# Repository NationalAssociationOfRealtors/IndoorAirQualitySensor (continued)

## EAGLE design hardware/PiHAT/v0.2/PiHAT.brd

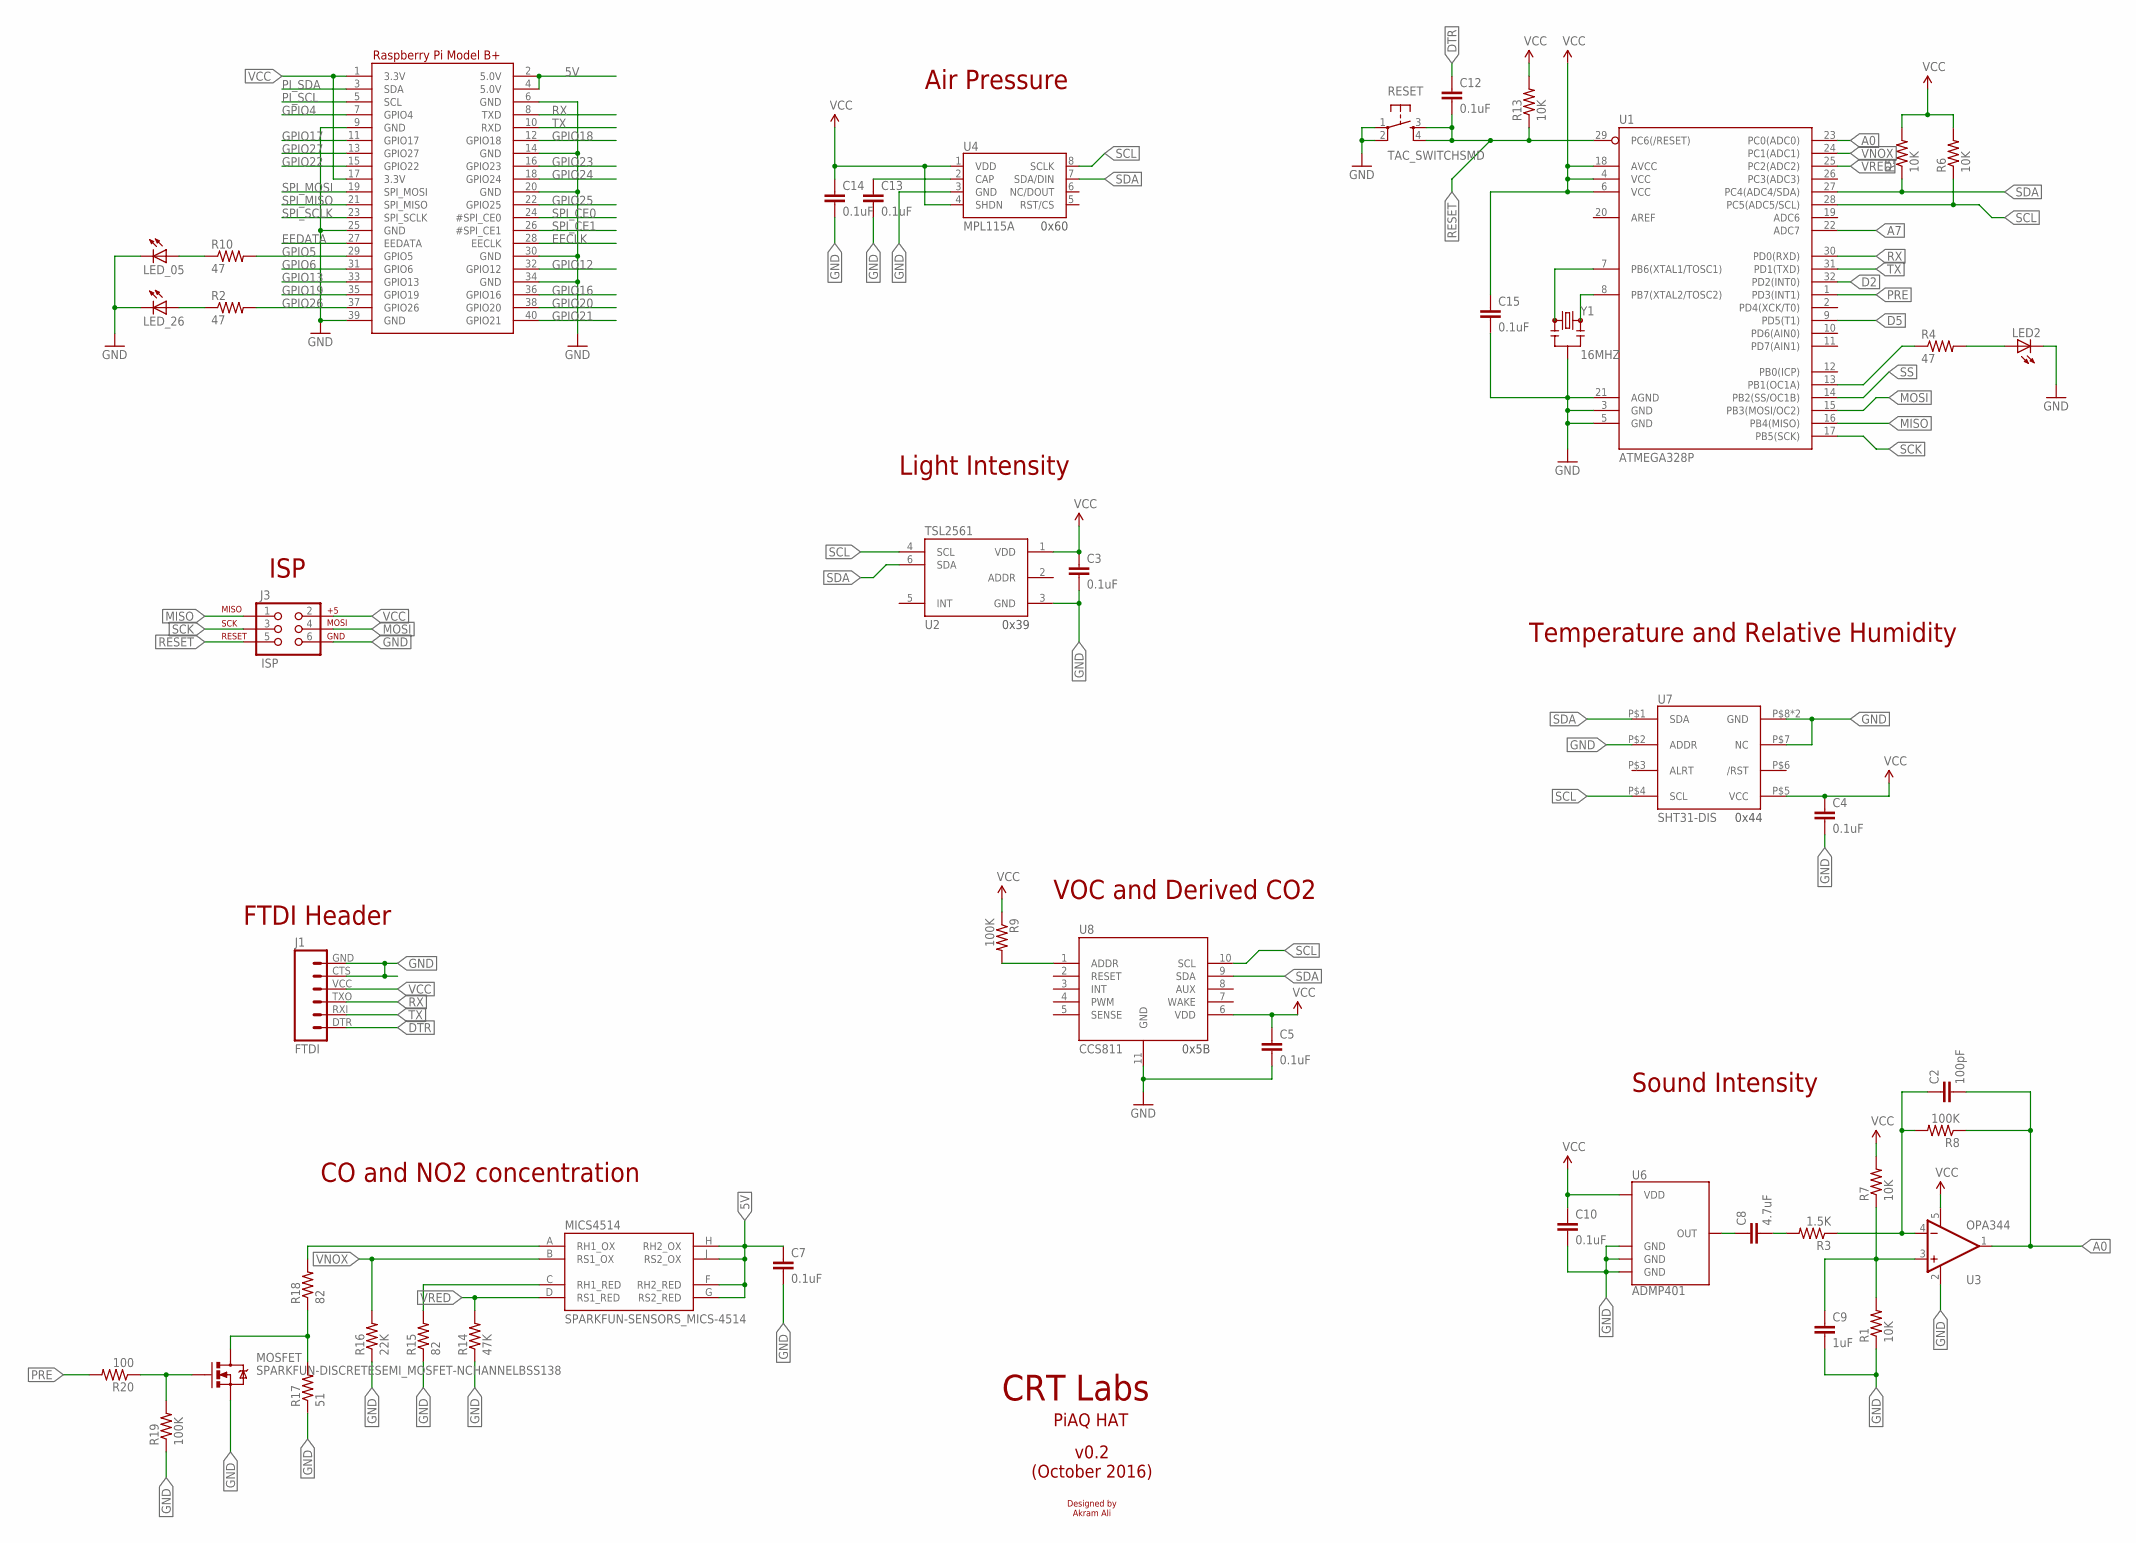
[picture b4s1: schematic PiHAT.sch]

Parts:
C2: 100pF; 0805; MPN CC0805JRNPO9BN101; DIGIKEY# 311-1111-1-ND
C3, C4, C5, C7, C10, C12, C13, C14, C15: 0.1uF; 0805; MPN CC0603KRX7R7BB104; DIGIKEY# 311-1088-1-ND
C8: 4.7uF; 0805; MPN CC0805KKX5R8BB475; DIGIKEY# 311-1871-1-ND
C9: 1uF; 0805; MPN CC0805KKX7R7BB105; DIGIKEY# 311-1365-1-ND
J1: FTDI; FTDI_BASIC; MPN FT231XS-R; DIGIKEY# 768-1129-1-ND
J3: ISP; 2X3
LED2: LEDCHIPLED_0805; CHIPLED_0805; MPN LY L29K-H1K2-26-Z; DIGIKEY# 475-1196-1-ND
LED_05, LED_26: LEDCHIPLED_0805; CHIPLED_0805; MPN LY L29K-H1K2-26-Z; DIGIKEY# 475-1196-1-ND
MICS4514: SPARKFUN-SENSORS_MICS-4514; SPARKFUN-SENSORS_MICS_10-SMD; MPN MiCS-4514
MOSFET: SPARKFUN-DISCRETESEMI_MOSFET-NCHANNELBSS138; SPARKFUN-DISCRETESEMI_SOT23-3; MPN BSS138-7-F; DIGIKEY# BSS138-FDICT-ND
R1, R5, R6, R7, R13: 10K; 0805; MPN RC0805JR-0710KL; DIGIKEY# 311-10KARCT-ND
R2, R4, R10: 47; 0805; MPN RC0805JR-0747RL; DIGIKEY# 311-47ARCT-ND
R3: 1.5K; 0805; MPN RT0805BRD071K5L; DIGIKEY# YAG1814CT-ND
R8, R9: 100K; 0805; MPN RC0805FR-07100KL; DIGIKEY# 541-82.0CCT-ND
R14: 47K; 0805; MPN ESR10EZPJ473; DIGIKEY# RHM47KKCT-ND
R15, R18: 82; 0805; MPN CRCW080582R0FKEA; DIGIKEY# 541-82.0CCT-ND
R16: 22K; 0805; MPN RC0805JR-0722KL; DIGIKEY# 311-22KARCT-ND
R17: 51; 0805; MPN ESR10EZPJ510; DIGIKEY# RHM51KCT-ND
R19: 100K; 0805; MPN RC0805FR-07100KL; DIGIKEY# 311-100KCRCT-ND
R20: 100; 0805; MPN RC0805FR-07100RL; DIGIKEY# 311-100CRCT-ND
RESET: TAC_SWITCHSMD; TACTILE-SWITCH-SMD; MPN PTS525SM15SMTR2 LFS; DIGIKEY# CKN9104CT-ND
RPI1: RASPBERRYPI_BPLUS_HATSLOTS; PI_HAT_SLOTS
U1: ATMEGA328P; TQFP32-08; MPN ATMEGA328PB-AU; DIGIKEY# ATMEGA328P-AU-ND
U2: TSL2561; FN-6; MOUSER# 856-TSL2561T; DIGIKEY# TSL2561-FNCT-ND
U3: OPA344; SOT23-5; MPN OPA344NA/3K; DIGIKEY# 296-41475-1-ND
U4: MPL115A; LGA8; MPN MPL115A2; DIGIKEY# MPL115A2-ND
U6: ADMP401; MPN INMP401ACEZ-R7; DIGIKEY# INMP401ACEZ-R7CT-ND
U7: SHT31-DIS; SHT3X; MPN SHT31-DIS-B; DIGIKEY# 1649-1011-1-ND
U8: CCS811; LGA; MPN CCS811
Y1: 16MHZ; RESONATOR-SMD; MPN CSTCE16M0V53-R0; DIGIKEY# 490-1198-1-ND

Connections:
5V: C7.1, MICS4514.F (RH2_RED), MICS4514.G (RS2_RED), MICS4514.H (RH2_OX), MICS4514.J (RS2_OX), RPI1.2 (5.0V), RPI1.4 (5.0V)
A0: C2.2, R8.1, U1.23 (PC0(ADC0)), U3.1 (OUT)
A7: U1.22 (ADC7)
D2: U1.32 (PD2(INT0))
D5: U1.9 (PD5(T1))
DTR: C12.1, J1.DTR (1)
EECLK: RPI1.28 (EECLK)
EEDATA: RPI1.27 (EEDATA)
GND: C3.2, C4.2, C5.2, C7.2, C9.2, C10.2, C13.2, C14.2, C15.2, J1.CTS (5), J1.GND (6), J3.6, LED2.C, LED_05.C, LED_26.C, MOSFET.2 (S), R1.1, R14.1, R15.1, R16.1, R17.1, R19.1, RESET.1, RESET.2, RPI1.6 (GND), RPI1.9 (GND), RPI1.14 (GND), RPI1.20 (GND), RPI1.25 (GND), RPI1.30 (GND), RPI1.34 (GND), RPI1.39 (GND), U1.3 (GND), U1.5 (GND), U1.21 (AGND), U2.3 (GND), U3.2 (V-), U4.3 (GND), U6.2 (GND), U6.4 (GND), U6.6 (GND), U7.P$2 (ADDR), U7.P$7 (NC), U7.P$8 (GND), U7.PAD (GND), U8.11 (GND), Y1.2
GPIO4: RPI1.7 (GPIO4)
GPIO5: R10.2, RPI1.29 (GPIO5)
GPIO6: RPI1.31 (GPIO6)
GPIO12: RPI1.32 (GPIO12)
GPIO13: RPI1.33 (GPIO13)
GPIO16: RPI1.36 (GPIO16)
GPIO17: RPI1.11 (GPIO17)
GPIO18: RPI1.12 (GPIO18)
GPIO19: RPI1.35 (GPIO19)
GPIO20: RPI1.38 (GPIO20)
GPIO21: RPI1.40 (GPIO21)
GPIO22: RPI1.15 (GPIO22)
GPIO23: RPI1.16 (GPIO23)
GPIO24: RPI1.18 (GPIO24)
GPIO25: RPI1.22 (GPIO25)
GPIO26: R2.2, RPI1.37 (GPIO26)
GPIO27: RPI1.13 (GPIO27)
MISO: J3.1, U1.16 (PB4(MISO))
MOSI: J3.4, U1.15 (PB3(MOSI/OC2))
unnamed: LED_26.A, R2.1
unnamed: R4.1, U1.13 (PB1(OC1A))
unnamed: LED2.A, R4.2
unnamed: U1.8 (PB7(XTAL2/TOSC2)), Y1.3
unnamed: U1.7 (PB6(XTAL1/TOSC1)), Y1.1
unnamed: LED_05.A, R10.1
unnamed: C8.1, U6.1 (OUT)
unnamed: MICS4514.A (RH1_OX), R18.2
unnamed: C8.2, R3.2
unnamed: C2.1, R3.1, R8.2, U3.4 (-IN)
unnamed: C9.1, R1.2, R7.1, U3.3 (+IN)
unnamed: C13.1, U4.2 (CAP)
unnamed: MICS4514.C (RH1_RED), R15.2
unnamed: R9.2, U8.1 (ADDR)
unnamed: MOSFET.3 (D), R17.2, R18.1
unnamed: MOSFET.1 (G), R19.2, R20.1
PI_SCL: RPI1.5 (SCL)
PI_SDA: RPI1.3 (SDA)
PRE: R20.2, U1.1 (PD3(INT1))
RESET: C12.2, J3.5, R13.1, RESET.3, RESET.4, U1.29 (PC6(/RESET))
RX: J1.TXO (3), RPI1.8 (TXD), U1.30 (PD0(RXD))
SCK: J3.3, U1.17 (PB5(SCK))
SCL: R6.1, U1.28 (PC5(ADC5/SCL)), U2.4 (SCL), U4.8 (SCLK), U7.P$4 (SCL), U8.10 (SCL)
SDA: R5.1, U1.27 (PC4(ADC4/SDA)), U2.6 (SDA), U4.7 (SDA/DIN), U7.P$1 (SDA), U8.9 (SDA)
SPI_CE0: RPI1.24 (#SPI_CE0)
SPI_CE1: RPI1.26 (#SPI_CE1)
SPI_MISO: RPI1.21 (SPI_MISO)
SPI_MOSI: RPI1.19 (SPI_MOSI)
SPI_SCLK: RPI1.23 (SPI_SCLK)
SS: U1.14 (PB2(SS/OC1B))
TX: J1.RXI (2), RPI1.10 (RXD), U1.31 (PD1(TXD))
VCC: C3.1, C4.1, C5.1, C10.1, C14.1, C15.1, J1.VCC (4), J3.2, R5.2, R6.2, R7.2, R9.1, R13.2, RPI1.1 (3.3V), RPI1.17 (3.3V), U1.4 (VCC), U1.6 (VCC), U1.18 (AVCC), U2.1 (VDD), U3.5 (V+), U4.1 (VDD), U4.4 (SHDN), U6.5 (VDD), U7.P$5 (VCC), U8.6 (VDD)
VNOX: MICS4514.B (RS1_OX), R16.2, U1.24 (PC1(ADC1))
VRED: MICS4514.D (RS1_RED), R14.2, U1.25 (PC2(ADC2))

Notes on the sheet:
Light Intensity
VOC and Derived CO2
Air Pressure
Sound Intensity
Temperature and Relative Humidity
ISP
CO and NO2 concentration
CRT Labs
PiAQ HAT
v0.2 (October 2016)
Designed by Akram Ali
0x39
0x60
0x5B
0x44
FTDI Header

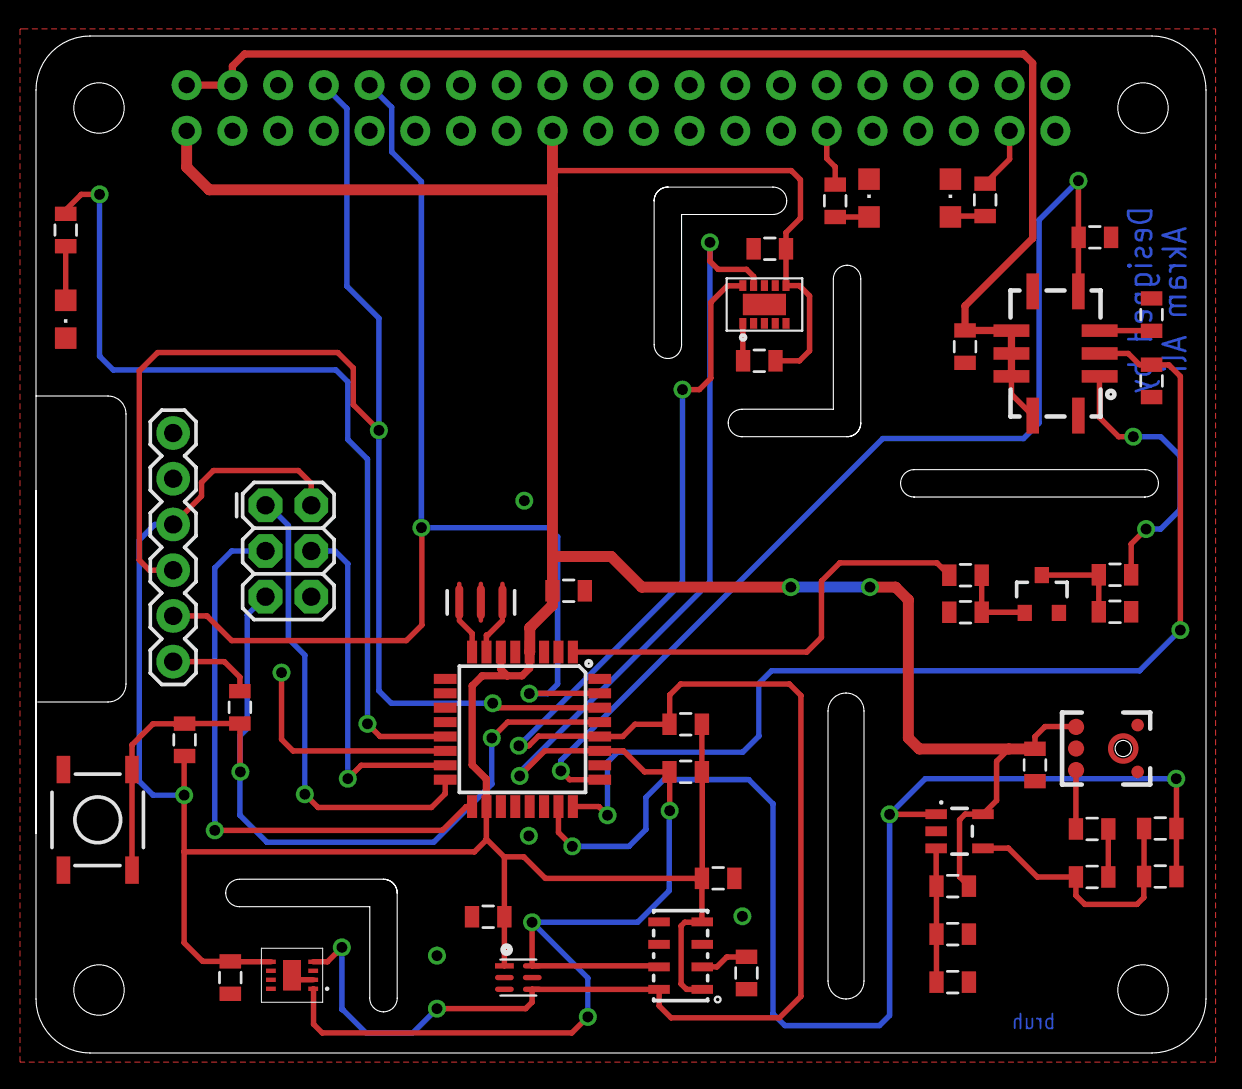
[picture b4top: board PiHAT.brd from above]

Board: 2 copper layers, 65.0 x 56.5 mm, 47 parts (0 on the bottom side), 34 nets.

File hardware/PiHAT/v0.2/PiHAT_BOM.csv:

Part,Value,Device,Package,Description,DIGIKEY#,MANF,MANF#,MF,MOUSER#,MPN,NO_BOM
C2,100pF,CAP0805,805,Capacitor,311-1111-1-ND,,,,,CC0805JRNPO9BN101,
C3,0.1uF,CAP0805,805,Capacitor,311-1088-1-ND,,,,,CC0603KRX7R7BB104,
C4,0.1uF,CAP0805,805,Capacitor,311-1088-1-ND,,,,,CC0603KRX7R7BB104,
C5,0.1uF,CAP0805,805,Capacitor,311-1088-1-ND,,,,,CC0603KRX7R7BB104,
C7,0.1uF,CAP0805,805,Capacitor,311-1088-1-ND,,,,,CC0603KRX7R7BB104,
C8,4.7uF,CAP0805,805,Capacitor,311-1871-1-ND,,,,,CC0805KKX5R8BB475,
C9,1uF,CAP0805,805,Capacitor,311-1365-1-ND,,,,,CC0805KKX7R7BB105,
C10,0.1uF,CAP0805,805,Capacitor,311-1088-1-ND,,,,,CC0603KRX7R7BB104,
C12,0.1uF,CAP0805,805,Capacitor,311-1088-1-ND,,,,,CC0603KRX7R7BB104,
C13,0.1uF,CAP0805,805,Capacitor,311-1088-1-ND,,,,,CC0603KRX7R7BB104,
C14,0.1uF,CAP0805,805,Capacitor,311-1088-1-ND,,,,,CC0603KRX7R7BB104,
C15,0.1uF,CAP0805,805,Capacitor,311-1088-1-ND,,,,,CC0603KRX7R7BB104,
J1,FTDI,FTDI_BASICPTH,FTDI_BASIC,FTDI Basic header with labels,768-1129-1-ND,,,,,FT231XS-R,
LED2,,LEDCHIPLED_0805,CHIPLED_0805,LED,475-1196-1-ND,,,,,LY L29K-H1K2-26-Z,
LED_05,,LEDCHIPLED_0805,CHIPLED_0805,LED,475-1196-1-ND,,,,,LY L29K-H1K2-26-Z,
LED_26,,LEDCHIPLED_0805,CHIPLED_0805,LED,475-1196-1-ND,,,,,LY L29K-H1K2-26-Z,
MICS4514,SPARKFUN-SENSORS_MICS-4514,SPARKFUN-SENSORS_MICS-4514,SPARKFUN-SENSORS_MICS_10-SMD,Metal oxide MEMS carbon monoxide (CO) and NOx sensor in an SMD package.,,SensorTech,,,,MiCS-4514,
MOSFET,SPARKFUN-DISCRETESEMI_MOSFET-NCHANNELBSS138,SPARKFUN-DISCRETESEMI_MOSFET-NCHANNELBSS138,SPARKFUN-DISCRETESEMI_SOT23-3,Common NMOSFET Parts,BSS138-FDICT-ND,,,,,BSS138-7-F,
R1,10K,RESISTOR0805-RES,805,Resistor,311-10KARCT-ND,,,,,RC0805JR-0710KL,
R2,47,RESISTOR0805-RES,805,Resistor,311-47ARCT-ND,,,,,RC0805JR-0747RL,
R3,1.5K,RESISTOR0805-RES,805,Resistor,YAG1814CT-ND,,,,,RT0805BRD071K5L,
R4,47,RESISTOR0805-RES,805,Resistor,311-47ARCT-ND,,,,,RC0805JR-0747RL,
R5,10K,RESISTOR0805-RES,805,Resistor,311-10KARCT-ND,,,,,RC0805JR-0710KL,
R6,10K,RESISTOR0805-RES,805,Resistor,311-10KARCT-ND,,,,,RC0805JR-0710KL,
R7,10K,RESISTOR0805-RES,805,Resistor,311-10KARCT-ND,,,,,RC0805JR-0710KL,
R8,100K,RESISTOR0805-RES,805,Resistor,541-82.0CCT-ND,,,,,RC0805FR-07100KL,
R9,100K,RESISTOR0805-RES,805,Resistor,541-82.0CCT-ND,,,,,RC0805FR-07100KL,
R10,47,RESISTOR0805-RES,805,Resistor,311-47ARCT-ND,,,,,RC0805JR-0747RL,
R13,10K,RESISTOR0805-RES,805,Resistor,311-10KARCT-ND,,,,,RC0805JR-0710KL,
R14,47K,RESISTOR0805-RES,805,Resistor,RHM47KKCT-ND,,,,,ESR10EZPJ473,
R15,82,RESISTOR0805-RES,805,Resistor,541-82.0CCT-ND,,,,,CRCW080582R0FKEA,
R16,22K,RESISTOR0805-RES,805,Resistor,311-22KARCT-ND,,,,,RC0805JR-0722KL,
R17,51,RESISTOR0805-RES,805,Resistor,RHM51KCT-ND,,,,,ESR10EZPJ510,
R18,82,RESISTOR0805-RES,805,Resistor,541-82.0CCT-ND,,,,,CRCW080582R0FKEA,
R19,100K,RESISTOR0805-RES,805,Resistor,311-100KCRCT-ND,,,,,RC0805FR-07100KL,
R20,100,RESISTOR0805-RES,805,Resistor,311-100CRCT-ND,,,,,RC0805FR-07100RL,
RESET,TAC_SWITCHSMD,TAC_SWITCHSMD,TACTILE-SWITCH-SMD,Momentary Switch,CKN9104CT-ND,,,,,PTS525SM15SMTR2 LFS,
U1,ATMEGA328P,ATMEGA328P_TQFP,TQFP32-08,,ATMEGA328P-AU-ND,,,,,ATMEGA328PB-AU,
U2,TSL2561,TSL2561FN,FN-6,TSL2561 illumination sensor,TSL2561-FNCT-ND,AMS-TAOS-USA-Inc.,TSL2561FN,,856-TSL2561T,TSL2561FN,
U3,OPA344,OPA344,SOT23-5,Single gate rail-to-rail output op-amp. Inputs extend 300mV past rails.,296-41475-1-ND,,,,,OPA344NA/3K,
U4,MPL115A,MPL115A,LGA8,MPL115A1 (SPI) and MPL115A2 (I2C) Miniature Digital Barometer,MPL115A2-ND,,,,,MPL115A2,
U6,ADMP401,ADMP401,ADMP401,Omnidirection bottom-port MEMS microphone,INMP401ACEZ-R7CT-ND,,,,,INMP401ACEZ-R7,
U7,SHT31-DIS,SHT31-DIS,SHT3X,,1649-1011-1-ND,,,,,SHT31-DIS-B,
U8,CCS811,CCS811-I2C,LGA,,,AMS,,,,CCS811,
Y1,16MHZ,RESONATOR16MHZ,RESONATOR-SMD,Resonator,490-1198-1-ND,,,,,CSTCE16M0V53-R0,

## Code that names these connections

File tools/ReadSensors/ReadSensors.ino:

/*
  Sensor Board v0.3
  Measures Temperature, Relative Humidity, Light intensity,
  Air pressure (and derived altitude), Sound intensity,
  concentrations of CO, NO2, VOC (derived) and CO2 (derived)

  Currently untested: TSL2561 light sensor code
  Currently untested: MAX4466 mic + amp code
  
  Designed at CRT Labs (July 2016)
  https://github.com/NationalAssociationOfRealtors/SensorBoard
  
  Modified: 6 September 2016
  by Akram Ali
 */

// define libraries
#include <Arduino.h>
#include <Wire.h>
#include "Adafruit_SHT31.h"
#include "SparkFunMPL3115A2.h"
#include <Adafruit_Sensor.h>
#include <Adafruit_TSL2561_U.h>

// define objects
MPL3115A2 myPressure;
Adafruit_SHT31 sht31 = Adafruit_SHT31();
Adafruit_TSL2561_Unified tsl = Adafruit_TSL2561_Unified(TSL2561_ADDR_FLOAT, 12345);

// define IAQ core global variables
#define iaqaddress 0x5A
uint16_t predict;
uint8_t statu;
int32_t resistance;
uint16_t tvoc;

// define MICS-4514 global variables
#define PRE_PIN          8
#define VNOX_PIN         A0
#define VRED_PIN         A1
#define PRE_HEAT_SECONDS 10
int vnox_value = 0;
int vred_value = 0;

// define TSL2561 global variables
long lux;

void setup()
{
  Serial.begin(115200);
  Serial.println("Setup");

  pinMode(9, OUTPUT);  // pin 9 controls LED
  pinMode(5, OUTPUT);   // pin 5 controls power to all sensors
  digitalWrite(5, HIGH);  // turn all sensors on
  delay(10);

  pinMode(PRE_PIN, OUTPUT);  // set preheater pin for mics4514 gas sensor
  Serial.print("MICS-4514 Preheating...");
  // Wait for preheating
  digitalWrite(PRE_PIN, 1);
  delay(PRE_HEAT_SECONDS * 1000);
  digitalWrite(PRE_PIN, 0);
  Serial.println("Done");
  
}

// the loop function runs over and over again forever
void loop()
{
  digitalWrite(9, HIGH);   // turn the LED on (HIGH is the voltage level)
  delay(1000);              // wait for a second
  digitalWrite(9, LOW);    // turn the LED off by making the voltage LOW
  
  Serial.println("---------------------");
  
  // MAX 4466 amp
  //Serial.println(analogRead(A0));  // read sound levels
  //Serial.println();


  // TSL2561 light sensor
  tsl.begin(); 
  tsl.enableAutoRange(true);
  //tsl.setIntegrationTime(TSL2561_INTEGRATIONTIME_13MS);      /* fast but low resolution */
  tsl.setIntegrationTime(TSL2561_INTEGRATIONTIME_101MS);  /* medium resolution and speed   */
  // tsl.setIntegrationTime(TSL2561_INTEGRATIONTIME_402MS);  /* 16-bit data but slowest conversions */
  sensors_event_t event;
  tsl.getEvent(&event);
  if (event.light)
    lux = event.light;
  else
    lux = -1;
  Serial.print("Light intensity (lux): ");
  Serial.println(lux);
  
  // MICS 4514 CO/NO2 gas sensor
  // Read analog values, print them out, and wait
  vnox_value = analogRead(VNOX_PIN);
  vred_value = analogRead(VRED_PIN);
  Serial.print("Vnox: ");
  Serial.print(vnox_value, DEC);
  Serial.print(" Vred: ");
  Serial.println(vred_value, DEC);
  readCO();
  readNO2();

  
  // MPL3115A2 air pressure sensor
  myPressure.begin(); // Get pressure sensor online
  //Configure the sensor
  //myPressure.setModeAltimeter(); // Measure altitude above sea level in meters
  myPressure.setModeBarometer(); // Measure pressure in Pascals from 20 to 110 kPa
  
  myPressure.setOversampleRate(7); // Set Oversample to the recommended 128
  myPressure.enableEventFlags(); // Enable all three pressure and temp event flags 
  delay(10);
  
  float pressure = myPressure.readPressure();
  Serial.print("MPL3115A2 Pressure(Pa): ");
  Serial.println(pressure, 2);

  float temperature = myPressure.readTempF();
  Serial.print("MPL3115A2 Temp(f): ");
  Serial.println(temperature, 2);

  //const int station_elevation_ft = 5374; //Must be obtained with a GPS unit
  //float station_elevation_m = station_elevation_ft * 0.3048; //I'm going to hard code this
  const int station_elevation_m = 1638; //Accurate for the roof on my house
  //1 pascal = 0.01 millibars
  pressure /= 100; //pressure is now in millibars

  float part1 = pressure - 0.3; //Part 1 of formula
  
  const float part2 = 8.42288 / 100000.0;
  float part3 = pow((pressure - 0.3), 0.190284);
  float part4 = (float)station_elevation_m / part3;
  float part5 = (1.0 + (part2 * part4));
  float part6 = pow(part5, (1.0/0.190284));
  float altimeter_setting_pressure_mb = part1 * part6; //Output is now in adjusted millibars
  float baroin = altimeter_setting_pressure_mb * 0.02953;

  Serial.print("MPL3115A2 Altimeter setting InHg: ");
  Serial.println(baroin, 2);

  
  // SHT31 T/RH sensor 
  sht31.begin(0x44);
  Serial.print("SHT31 Temperature: ");
  Serial.println(sht31.readTemperature());
  Serial.print("SHT31 Humidity: ");
  Serial.println(sht31.readHumidity());
  

  // IAQ core
  Wire.requestFrom(iaqaddress, 9);
  predict = (Wire.read()<< 8 | Wire.read()); 
  statu = Wire.read();
  resistance = (Wire.read()& 0x00)| (Wire.read()<<16)| (Wire.read()<<8| Wire.read());
  tvoc = (Wire.read()<<8 | Wire.read());
  checkStatus();
  
  Serial.print("CO2 concentration:");
  Serial.println(predict);
  //Serial.print("IAQ core Status: ");
  //Serial.println(statu, HEX);
  Serial.print("IAQ core Resistance: ");
  Serial.println(resistance);
  Serial.print("TVoC concentration: ");
  Serial.println(tvoc);

  
  Serial.println();
  
  //digitalWrite(5, LOW);  // turn sensors off
  delay(5000);
}



void checkStatus()
{
  if(statu == 0x10)
  {
    Serial.println("IAQ Core Warming up...");
  }
  else if(statu == 0x00)
  {
    Serial.println("IAQ Core Ready");  
  }
  else if(statu == 0x01)
  {
    Serial.println("IAQ Core Busy");  
  }
  else if(statu == 0x80)
  {
    Serial.println("IAQ Core Error");  
  }
  else
  Serial.println("No Status, check IAQ Core");  
}



float readCO()
{
  float adc = analogRead(VNOX_PIN);
  float Rs = 47000.0/(1023.0/adc);
  float R0 = 82000.0;
  float ratio = Rs/R0;
  float concentration = ((-181.4)*log(ratio))-97.469;
  Serial.print("CO concentration (ppb): ");
  //Serial.println(adc);
  //Serial.println(Rs);
  //Serial.println(R0);
  //Serial.println(ratio);
  Serial.println(concentration);
  return concentration;
}

float readNO2()
{
  float adc = analogRead(VRED_PIN);
  float Rs = 22000.0/(1023.0/adc);
  float R0 = 350.0;
  float ratio = Rs/R0;
  float concentration = (124.28*log(ratio))-270.37;
  Serial.print("NO2 concentration (ppb): ");
  //Serial.println(adc);
  //Serial.println(Rs);
  //Serial.println(R0);
  //Serial.println(ratio);
  Serial.println(concentration);
  return concentration;
}

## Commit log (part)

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2016-07-27 Eagle files for sensor board
2016-07-28 Replaced 5V stepup with reg
    Replaced NCP1402 with MCP1703 (for MICS 4514 gas sensor)
2016-08-10 Adding Case Design and STL
2016-08-11 adding honeycomb airflow
2016-08-11 code cleanup
2016-08-11 added rounded corners, dir struxture
2016-08-11 flipping for easier print
2016-08-11 added slot for pinouts
2016-08-11 adding eagle lock files to ignore
2016-08-11 adding new stl
2016-08-12 logo text on side of case
2016-08-16 adding slide cover
2016-08-25 added labels to board and ftdi mapping instructions
2016-08-25 formatting
2016-09-06 Sensor board v0.2 Arduino test code
    Read all data in serial monitor.
    Untested: TSL2561
    Untested: MAX4466
2016-09-06 Replaced mic
2016-09-07 Added RFM69 pads, FTDI chip, USB-microB, bug fixes
2016-09-07 first commit of radio board
2016-09-07 Changed font size of labels
2016-09-08 updating git ignore with eagle lock files
2016-09-08 directory organization
2016-09-08 adding professional shots and updating readme
2016-09-08 updating description
2016-09-08 adding capabilities to README
2016-09-08 adding tool to read sensor data for initial testing
2016-09-08 prepping for hardware version 3.0
2016-09-08 adding license
2016-09-08 adding v3 images
2016-09-08 Updating license to Apache 2
2016-09-08 modifying v3 enclosure and fixing typo on sensor board v3 schematic
2016-09-08 OSH Park render
2016-09-08 Moved hidden labels to tNames layer
2016-09-08 Moved labels to _tsilk layer (121)
2016-09-08 Added PDF schematic
2016-09-08 Adjusted some traces
2016-09-09 Added SMA connector for antenna
2016-09-09 Minor touches
2016-09-09 Removed 'label' from SMA connector
2016-09-09 Added v0.4 OSH park render
2016-09-09 Update README.md
    Added sensor model numbers
2016-09-10 syntax on scad
2016-09-10 naming conventions
2016-09-10 fixed link
2016-09-14 Created v0.5
2016-09-14 Removed NPN transistor
    connected everything to common GND
2016-09-14 Increased thickness of power lines to 16
2016-09-14 Added decoupling cap for ATmega328P
    0.1uF
2016-09-14 Rearranged status LED
    and decoupling cap
2016-09-14 Added extra GND vias
2016-09-14 Adjusted some traces around MCU
2016-09-14 Added v0.5 PDF schematic
2016-09-15 Made the GND plane more consistent
2016-09-15 Connected GND plane
2016-09-15 Added PiHAT
2016-09-15 Removed FTDI, RFM69, USB
2016-09-15 started mapping sensors for pi hat
2016-09-16 Minor touch up of some traces
    near TSL2561 and SHT31
2016-09-16 Verrrrrry minor adjustments
    ¯\_(ツ)_/¯
2016-09-19 sensor board BOM
2016-09-19 Fixed several traces
2016-09-19 Updated silkscreen
2016-09-19 Added CRT Labs logo, gerber files
2016-09-23 Rename
2016-09-26 Added v0.3 photo
2016-09-27 Added sensor board node firmware
2016-09-28 Moved Trace on PiAQ, v4 of enclosure
2016-09-29 updating bom and iaq-case v4
2016-10-03 v0.6 - Major design update
    - Added CCS811 gas sensor (replaced IAQ core)
    - Added thermal isolation for all sensors
    - Rearranged all components to accommodate for thermal isolation
    - Ripped up all traces and rerouted them based on new arrangement
    - Temporarily removed ADMP401 mic + opamp (previous design was
    incorrect; requires envelop follower circuit for sound intensity
2016-10-05 Create master branch via GitHub
2016-10-05 Update CNAME
2016-10-05 organizing web directory
2016-10-05 v0.1 of piaq.io
2016-10-05 started adding links to schematics and data sheets
2016-10-05 adding images
2016-10-05 added link to board
2016-10-05 continuing to add BOM materials
2016-10-05 removing chars from BOM
2016-10-05 updating descriptions on bom
2016-10-05 adding piaq to home page
2016-10-05 updating faq
2016-10-05 finishing up faq
2016-10-05 typo fix
2016-10-05 Added 5x2 header attribute
    Digikey part number
2016-10-05 Updated BOM
    Digikey part number for MOSFET
2016-10-05 adding Photo Booth pics
2016-10-05 rolling in new photos
2016-10-05 spacing
2016-10-06 updated photo
    color corrected
2016-10-06 updated photos
    color corrected/full rez
2016-10-06 reorganizing photos
2016-10-06 rename file
2016-10-06 change images
    new color corrected images
2016-10-06 Moved files to separate folder
    v0.1
2016-10-06 adding head to faq page
2016-10-06 Updated PiAQ HAT to v0.2
    - Added LEDs on GPIO 05, 26
    - Replaced IAQ Core with CCS811
    - Added more thermal isolation and rerouted traces
    - Minor silkscreen adjustments
2016-10-06 Minor fixes to sensor board v0.6
2016-10-06 Added environmental parameters to silkscreen
2016-10-06 Minor trace fix
2016-10-06 Trace adjustments
2016-10-06 I2C pullups silkscreen
2016-10-06 Fixed layers
2016-10-06 Added FTDI headers to Pi HAT, separated ISP headers
2016-10-06 removed dupe data sheet
2016-10-06 Power trace adjustment
2016-10-06 v0.7 - Added mounting holes to the board
    - Dimension change
    - curved edges
2016-10-06 Adjusted microUSB port towards the edge
2016-10-06 cap trace adjustment
2016-10-07 v2 gerber files
2016-10-07 adding MPN to v2 schematics
2016-10-07 Sensor Node Photo
2016-10-07 adding details to aid in fabrication
2016-10-11 Renamed file names for each version
2016-10-18 v0.8 - Replaced MPL3115A2 with BMP280
    BMP280 is lower power and more accurate
2016-10-19 no longer needed as piaq is hosted in a separate repo
    http://piaq.crtlabs.org
2016-10-19 clarifying language regarding PiAQ separation
2016-10-22 Added traces for WAKE and INT pin
    CCS811 requires WAKE pin to be triggered before every communication. INT
    can be useful in the future for lower power or threshold alerts.
2016-10-22 Updated CCS811 lbr
    slightly smaller pads
2016-10-22 Updated CCS811 lbr
2016-10-23 Replaced FT231X SSOP with QFN package
    New part number: FT231XQ-R
    Adjusted several traces for the new package
2016-10-23 Silkscreen adjustments
    Diode direction
2016-10-23 Adjusted distance between MISO and MOSI vias
2016-10-23 Minor component adjustments
2016-10-23 Moved silkscreen values to layer 121
2016-10-24 removing bloat related to piaq
2016-10-25 adding links to libraries
    eventually will move these to readme
2016-10-25 Added OSH Park render
2016-11-28 began cleanup of repository in preparation of release
2016-11-28 cleaned up v0.5 firmware
2016-11-30 Corrected resistor and capacitor values for voltage ref.
    Also added adjusted CCS811 tstop pads
2016-11-30 Added v0.8 firmware
2017-01-03 updated LED descriptions
2017-01-04 adding bom to readme
2017-01-11 Remove BOD disable in software
2017-01-24 v0.51 - design update
    - Removed MICS sensor - was getting too hot and throwing temp sensor off. Also didn't give any sensible readings
    - Relocated SHT31 sensor to edge of board and added thermal cutouts to allow more accurate readings
    - Adjusted some components and rerouted traces
    - Removed reset button (not necessary anymore)
    - Adjusted silkscreen
2017-01-24 Adjusted one via to align with the 'o' of 'Board'
    because ¯\_(ツ)_/¯
2017-01-24 Gerber files added
    For https://www.seeedstudio.com/fusion_pcb.html
2017-02-17 v0.52 - major design update
    - Added mounting holes
    - Rearranged every single component for new board dimensions
    - Temporarily removed SMA edge mounted connector
    - RFM69 radio is now munted on top
    - Made ground pour more even + extra GND vias for proper stitching
2017-02-21 Added fiducial markers on PCB
2017-02-23 Added v0.51 firmware
2017-02-27 v0.53 added
    - Replaced TSL2561 with TSL2591 (former was approaching end of life)
2017-03-01 Update - Features added
    - Replaced regular LED with RGB LED (NeoPixel from Adafruit)
    - Adjusted overall dimensions to give slightly higher tolerance for mounting holes
    - I2C pins broken out to headers
    - Two digital pins broken out (for software serial)
    - Extra power pins broken out (for powering external devices or connecting ground)
2017-03-01 BOM update - added MPNs
2017-03-01 BOM update
2017-03-01 Updated SHT31/35 library
    Replaced old library with Adafruit version - slightly longer pads to avoid potential bridging during reflow.
2017-03-08 v0.53 - update
    - Aligned light sensor with RGB LED
    - Moved jumpers location after moving light sensor
    - Added PM2.5 jumpers (RX/TX/PWR/GND)
    - Adjusted some passive components
    - Several trace adjustments
    - Slightly increased board dimensions for added tolerance on mounting
2017-03-08 v0.53 - update
    - (previous commit: Replaced 10-pin header with 6-pin ISP header)
    - This commit: Added 1K resistors in series with FTDI's RX/TX line to
    give priority to external serial devices (unplug external device to
    program the board)
    - Some trace/silkscreen adjustments
2017-03-08 Fixed attributes
    Updated MPN for 1K ohm resistor
2017-03-14 v0.91 - Features updated
    LMP91000 circuit updated - Added ADS1115 16-bit ADC
2017-03-14 Updated SHT31 library
2017-03-14 Design update
    Replaced TSL2561 with TSL2591 sensor
    Rearranged a few traces around the CCS811 sensor
2017-03-22 BOM update
    - Added MPN for 0.1 and 10uF
    - Added I2C address and value for SHT35 on schematic
2017-03-28 Added v0.54 firmware
    - support for TSL2591 sensor
    - support for NeoPixel
2017-03-30 v0.55 - Trace antenna
    - Changed RFM69HW to RFM69HCW (smaller + better antenna pad placement)
    - Changed board dimensions to be a square (56.4mm)
    - Added a simple printed circuit whip (stub) trace antenna following
    this guide: http://www.hoperf.com/upload/rf/ANTENNAS_MODULE.pdf
    - Adjusted some traces to accomodate for new radio
    - Adjusted silkscreen
2017-03-31 v0.54 update - resonator library changed
    - Replaced previous resonator library (thinner pads, incorrectly
    aligned, usually got lucky) with one that has fatter pads (from RFM69
    USB gateway)
2017-04-05 v0.55 - Major design update
    - Added 2x5 header for PMS7003 PM sensor
    - Moved microphone+amp circuitry to accomodate for the PM sensor header
    - Removed UART and software serial breakout headers
    - Moved voltage regulator circuitry in space created by removing UART
    header
    - Moved LED in space created by moving voltage regulator
2017-04-05 Rename version number
    - Experimental trace antenna actually modification of v0.54
2017-04-11 v0.55 - major update 2
    - Added 915MHz chip antenna (JT 0868AT43A0020E) using ref. designs from:
    https://www.johansontechnology.com/datasheets/antennas/0868AT43A0020.pdf
    and http://www.ti.com/lit/an/swra160b/swra160b.pdf
    - Replaced RFM69HW with RFM69HCW to accomodate for space for chip
    antenna
    - Rerouted traces to accomodate for new parts
2017-04-17 Shifted IAQ core lower
    So it aligns with the Radio a bit more. Rerouted some traces and
    rearranged the decoupling cap
2017-04-17 Redesigned antenna trace
    - Removed trace for wire monopole (it needs GND plane underneath, so
    wouldn't have worked anyway)
    - Added jumper for SMD feed (if chip doesn't work, remove jumper, solder
    wire monopole directly to radio ANT pad
2017-05-08 Increased pin hole diameter for PM2.5 sensor
2017-05-08 Silkscreen updates
2017-05-11 Removed docs folder from v0.55
2017-05-12 Updated node ID variable
2017-05-12 add submodules for IEQ arduino libraries
2017-06-17 Added v0.56 EAGLE files
    Traces still incomplete
2017-06-20 Rearranged old files
2017-06-20 Added Power Booster circuit; a lot of rearrangments
    circuit traces still incomplete
2017-06-22 Added notches in the board
2017-06-23 v0.56 - completed
    DRC & ERC checked
    Features:
    - Board dimensions and component placement completely redesigned
    - Neopixel Mini replaced by NeoPixel Nano 2427
    - Light pipes for NeoPixel and Light sensor
    - SHT31 replaced with Si7021
2017-06-26 Trace and silkscreen adjustments
2017-06-29 Added another decoupling cap to ATMega328P
2017-07-11 Firmware updated for v0.56 board
2017-07-17 v0.56b - minor update
    - Moved CO2 sensor up the board
    - Updated library for light pipe
    - Adjusted components around the light pipe
    - Some silkscreen and trace adjustments
2017-07-17 Updated v0.56b with SMD pads for MH-z19 sensor
    - other minor trace, parts and silkscreen adjustments
2017-07-17 v0.56b - minor update
    silkscreen update and a couple of traces
